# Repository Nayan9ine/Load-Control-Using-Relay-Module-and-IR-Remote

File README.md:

# Load-Control-Using-Relay-Module-and-IR-Remote 
 
<p align="right">-By Nayan Ag</p>

#### Work Flow in Brief
IR salvaged from setup box  -> IR Protocol and Hex codes of remote found  -> Assigned alphanumeric value and commands to buttons -> Arranged separate power supply for LCD -> Installed a Light Bulb as load -> Assembled everything to create a working model

#### Components Used
IR Receiver, Arduino UNO CH340, Relay Module, Remote with IR transmitter, LCD with I2C, Light Bulb (as load), Jumper cables and 5V cable.
<br>

<table>
  <tr>
    <td>
    <br>  <div  align="center"><sub><i> Fig1:Setup Box</i></sub></div>
</td>
    <td>
    <br>  <div  align="center"><sub><i> Fig2: IR receiver on Setup Box</i></sub></div>
</td>
    <td>
    <br><div align="center"><sub><i> Fig3: IR receiver Desoldered</i></sub></div>
</td>
  </tr>
</table>

#### IR Receiver Extraction
Salvaged off from old tv setup box. Has 3 pins signal,gnd & power starting from left to right respectively (in fig 4). For desoldering I Used Chisel tip (greater surface area), ample amounts of flux and heat, tried removing old solder by desolder pump and copper wick also created a new solder bridge between the pins for effective heat distribution yet ultimately leading to a pin breaking. I soldered female to male type jumper cables to it (color coded) and used shrink tubes. 
<br>

<table>
  <tr>
    <td>
    <br>  <div  align="center"><sub><i> Fig4: IR Receiver</i></sub></div>
</td>
    <td>
    <br>  <div  align="center"><sub><i> Fig5: LDO on Setup Box</i></sub></div>
</td>
    <td>
    <br><div align="center"><sub><i> Fig6: LD1117AG ADA TBTQ</i></sub></div>
</td>
  </tr>
</table>

#### Finding IR Polarity
The old setup box wasn’t working, so couldn't measure using multimeter. So I backtracked the copper traces and found the component responsible for stepping down the main DC voltage and is usually kept near for EMI reduction. Shown in Fig 3: LD1117AG ADA TBTQ. It is a Low Dropout (LDO) linear positive voltage regulator manufactured by UTC (Unisonic Technologies). The ADA stands for adjustable so it needs to be configured by external resistors to supply 3.3v. I compared the connection of IR and LDO with LDO and Barrel jack Input of the circuit. Checked the resistor config. Ground was common to all and the one pin of IR not showing any continuity with LDO was the signal pin hence remains the power pin.

#### Using IR Library
Used IRremote library by Shirriff, z3t0, ArminJo (https://github.com/Arduino-IRremote/Arduino-IRremote). The library can detect numerous protocols used for communication by IR. Standard rgb light control Remote was used that uses NEC protocol. The library helped identify signal protocol and command code for each button pressed.
<br>

<p align="center">
  
   <div align="center"><sub><i> Fig7:Finding Remote Codes</i></sub></div>
</p>   

<div align="center"><sub><i> Fig8:NEC Protocol Used by Remote</i></sub></div>

#### About Code & Connection
Code was adjusted so that it integrates relay, LCD and assigning buttons values with numbers and letters. Removed or commented various sections of original code that was unnecessary after I found out my remote’s protocol. 
<br><br>

<p align="center"><br><sub><i>Fig9:RGB Remote</i></sub></p>
<br>

<p align="center"><sub><i>Fig10:Remote Button Codes</i></sub></p>
<br>

2 passwords declared in code one to turn relay on and other to turn off. Delay() of any value was causing timing issue hence leading to frozen response of lcd or ir. Baud rate of 115200 was utilized. Code only uploads when set back to 9600 for some reason and then turned back to 115200(I think it has something to do with CH340 chip). Millis() was used to debounce the buttons.
<br>
LCD with I2C used to show the status of relay and password entered. Backlight pins connected with 220ohm resistor and also LCD was supplied with separate 5v to reduce current draw.LCD connected with separate source with gnd common for both ext src and Arduino as sda and sdl do require gnd for reference.A USB A plug was stripped and power and gnd wire connected to IR. (Fig 11)
<br>

<table>
  <tr>
    <td>
    <br>  <div  align="center"><sub><i> Fig11 :5v USB A Plug</i></sub></div>
</td>
    <td>
    <br>  <div  align="center"><sub><i> Fig12 :5v USB A Plug</i></sub></div>
</td>
  </tr>
</table>

#### Current Requirements
Relay: 70-80mA per channel to energize the coil and 2-20mA to power the IR led in optocoupler, LCD backlight: 20-50mA, Arduino can provide : 400-450mA by USB ,500-800 by barrel jack (7v-12v).IR receiver 3.3v: 0.4-1.5ma on standby and 3-5mA at peak. During switching of relay rapid current burst occurs that causes fluctuation in LCD causing dim text appearance (due to voltage drop). To counter that capacitor can be used to be placed in parallel and delayed activation of LCD relay status indicator or in my case I used a totally separate source. 
<br>

<br><p align="center"> <sub><i>Fig13: Entire Setup (1)</i></sub>
<br>

<p align="center"> <sub><i>Fig14: Entire Setup (2)</i></sub></p>
<br>

<table>
  <tr>
    <td>
    <br>  <div  align="center"><sub><i> Fig15 :Turning ON</i></sub></div>
</td>
    <td>
    <br>  <div  align="center"><sub><i> Fig16 :Bulb is ON</i></sub></div>
</td>
  </tr>
</table>

<table>
  <tr>
    <td>
    <br>  <div  align="center"><sub><i> Fig17 :Turning OFF/i></sub></div>
</td>
    <td>
    <br>  <div  align="center"><sub><i> Fig18 :Bulb OFF</i></sub></div>
</td>
  </tr>
</table>

<table>
  <tr>
    <td>
    <br>  <div  align="center"><sub><i> Fig19 :Wrong Pass Used</i></sub></div>
</td>
    <td>
    <br>  <div  align="center"><sub><i> Fig20 :"RE-ENTER" Displayed</i></sub></div>
</td>
  </tr>
</table>

#### Kicad Design Images
Relay module was extracted from (https://github.com/ampnics/Relay-Module-HW-Design).<br>
<br>
<br>
<br>

#### Learning Outcomes
Serial.println(F("2")); //used in code <br>
Use of F: Stores memory in Flash instead of the temporary and small 2kb SRAM (Static Random Access Memory) in Arduino UNO. And as the code uses a lot of static texts (unchanging), we use flash memory. Variables that change shouldn’t be placed in flash as they need to be in SRAM to be updated.
<br>

Flash memory is permanent memory stored in Arduino. It stores the code even when unplugged. Static Variables stored in flash using F() macro.
<br><br>
In SRAM: there is stack and heap in a single memory column. Stack stores function call names and local variables and grows downwards. Heap stores dynamically stored data and grows upward. When memory gets full (called ‘stack overflow’) they both collide into each other and try overwriting each other causing random Arduino reboots and garbage outputs.
<br>

#### Possible Upgrades
password using cloud/wifi; buzzer integration for audio feedback; circuit design and wiring need to be made cleaner.

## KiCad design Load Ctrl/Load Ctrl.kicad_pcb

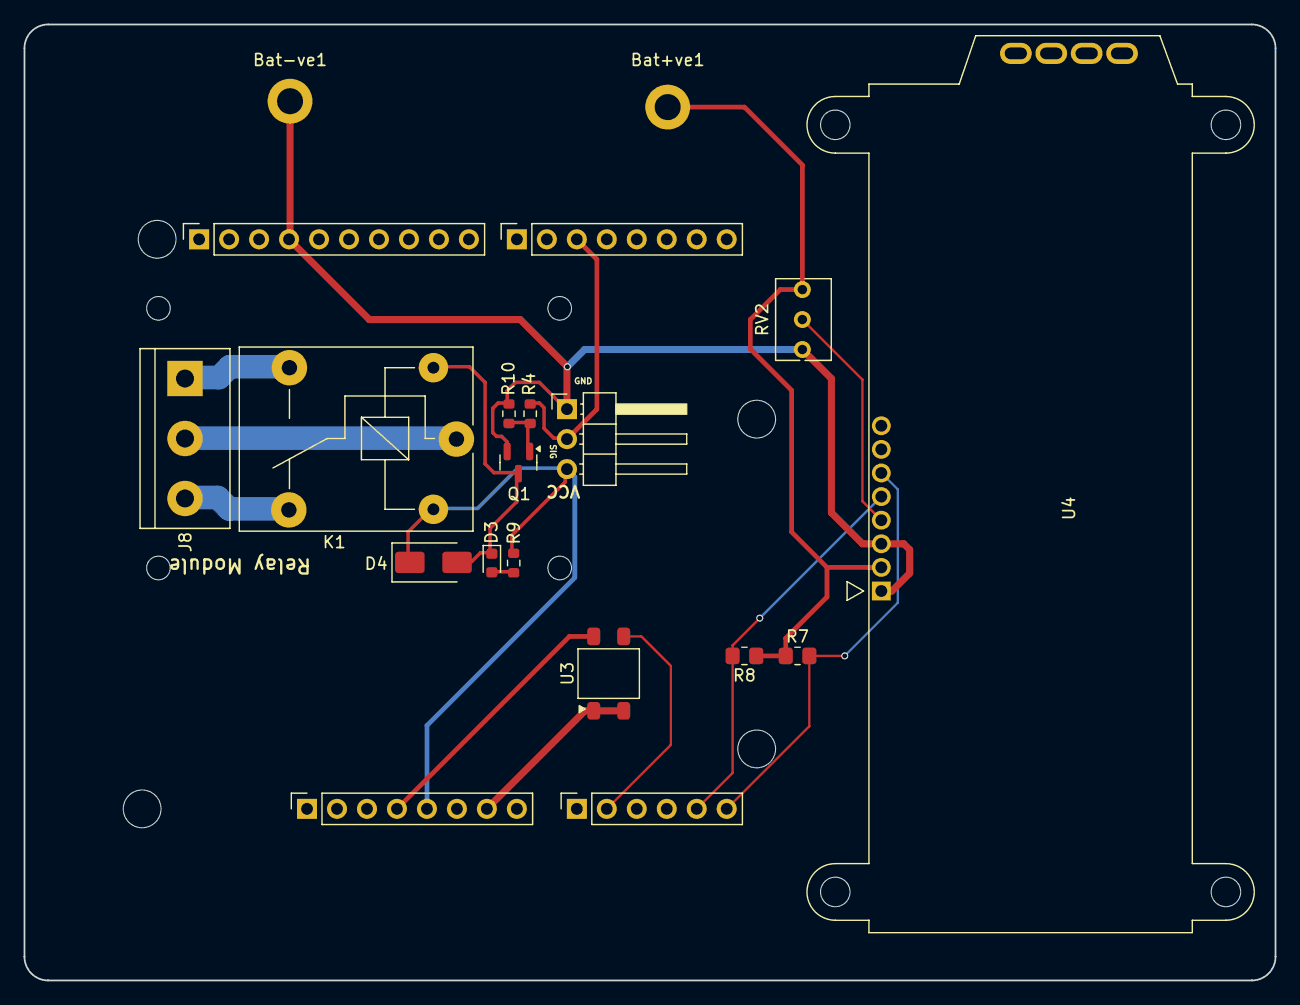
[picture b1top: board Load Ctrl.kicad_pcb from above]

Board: 2 copper layers, 106.0 x 81.0 mm, 24 parts (0 on the bottom side), 16 nets.

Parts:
Bat+ve1: MountingHole_Pad; MountingHole_2.2mm_M2_DIN965_Pad
Bat-ve1: MountingHole_Pad; MountingHole_2.2mm_M2_DIN965_Pad
D3: LED; LED_0603_1608Metric
D4: MRA4003T3G; D_SMA
J1: Power; PinSocket_1x08_P2.54mm_Vertical
J2: Digital/PWM; PinSocket_1x10_P2.54mm_Vertical
J3: Analog; PinSocket_1x06_P2.54mm_Vertical
J4: Digital/PWM; PinSocket_1x08_P2.54mm_Vertical
J7: Conn_01x03_Pin; PinHeader_1x03_P2.54mm_Horizontal
J8: Screw_Terminal_01x03; TerminalBlock_bornier-3_P5.08mm
K1: SANYOU_SRD_Form_C; Relay_SPDT_SANYOU_SRD_Series_Form_C
MH1, MH2, MH3, MH4: MountingHole_3.2mm
Q1: MMBT2222A; SOT-23
R4: 1K; R_0603_1608Metric
R7, R8: 4.7K; R_0805_2012Metric_Pad1.20x1.40mm_HandSolder
R9, R10: 10K; R_0603_1608Metric
RV2: Potentiometer; Potentiometer_Bourns_3266Y_Vertical
U3: IRM-H6xxT; Everlight_IRM-H6xxT
U4: EA_T123X-I2C; NHD-C0220BiZ-FSRGB

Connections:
+3V3: J1.4, U3.4 (Vcc)
+5V: D4.1 (K), J1.5, J7.3, K1.5, R9.1
/A1: J3.2, U3.3 (OUT)
/SCL/A5: J3.6, R7.2, U4.6 (SCL)
/SDA/A4: J3.5, R8.2, U4.5 (SDA)
/SIG: J4.3, J7.2, R4.1
/Vdd: Bat+ve1.1, R7.1, R8.1, RV2.1, U4.2 (VDD)
GND: Bat-ve1.1, J2.4, J7.1, Q1.2 (E), R10.2, RV2.3, U4.1 (VSS), U4.3 (VLCD)
GND1: J1.7, U3.1 (GND), U3.2 (GND)
unnamed: D3.2 (A), R9.2
unnamed: D3.1 (K), D4.2 (A), K1.2, Q1.3 (C)
unnamed: J8.1, K1.3
unnamed: J8.2, K1.1
unnamed: J8.3, K1.4
unnamed: Q1.1 (B), R4.2, R10.1
unnamed: RV2.2, U4.4 (V0)
